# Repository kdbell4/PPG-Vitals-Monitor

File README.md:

# PPG Vitals Monitor

A finger-clip vitals monitor built from scratch. Monitors standard vitals (heart rate, blood oxygen).

- Created with kicad schematic, which prototyped on a breadboard
  
  - PCB design is on the roadmap

- Firmware samples the output of the sensor, and a live plot tool reads those serial samples and generates a graph to analyze the waveform

- Finger Jig, a CAD model for holding the LED and photodiode in alignment across a finger

## Repo layout

| Path              | Contents                                                   |
| ----------------- | ---------------------------------------------------------- |
| `ppg_platformio/` | Teensy 4.0 firmware (PlatformIO + Arduino framework)       |
| `ppg_circuit/`    | KiCad project — schematic and PCB for the analog front end |
| `CAD/`            | FreeCAD parts                                              |

## Hardware Used

- **Photodiode**: BPW34
- **Op-amp**: MCP6002
- **MCU**: Teensy 4.0

## Signal Path for Sensor

```
Red + IR LEDs (660nm / 940nm)
        |
        v
   Finger (tissue) -- absorbs pulsing blood
        |
        v
Photodiode + TIA -- converts light to voltage
        |
        v
Passive filter + gain -- isolates the pulse signal
        |
        v
MCU: ADC + firmware -- heart rate, SpO2, bio-ID match
        |
        v
     Display -- vitals + identity
```

## CAD

3D-printed parts (`CAD/`) hold the LED and photodiode in stable optical
alignment across the fingertip. Built in FreeCAD; STLs are exported for slicing and
printing.

# Credits

- [XenGi](https://github.com/XenGi) for the Teensy symbol and footprint libraries for kicad
  
  - https://github.com/XenGi/teensy_library

- https://github.com/XenGi/teensy.pretty

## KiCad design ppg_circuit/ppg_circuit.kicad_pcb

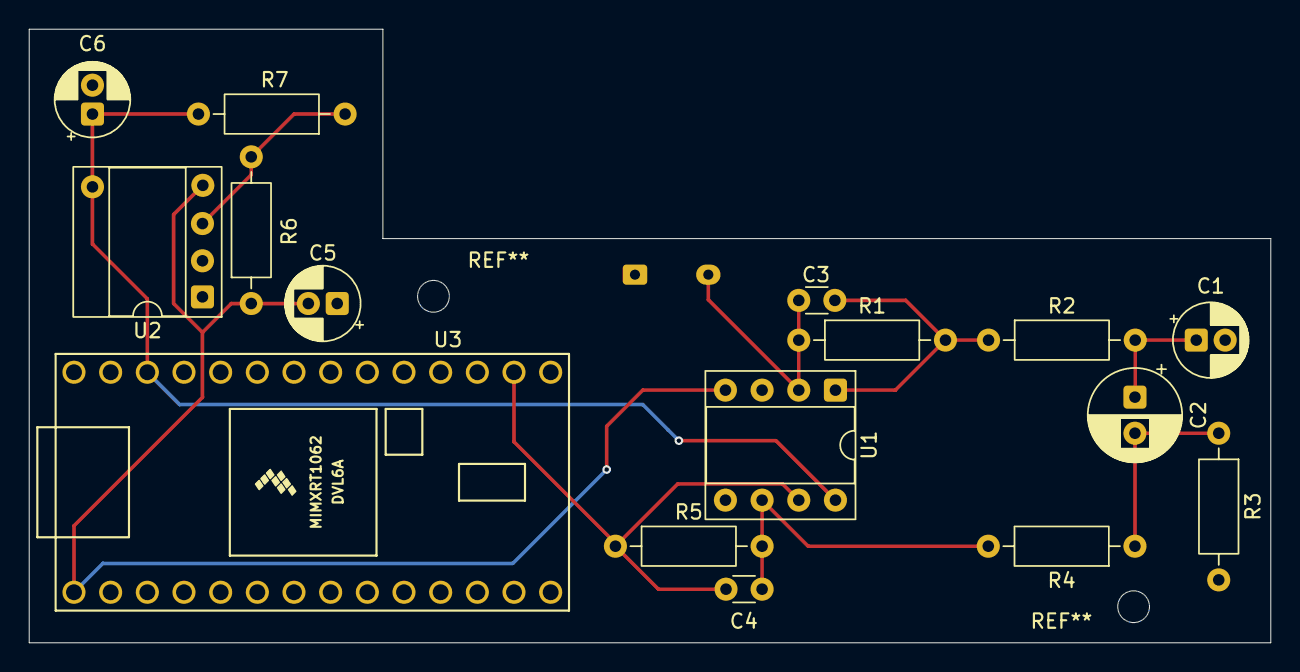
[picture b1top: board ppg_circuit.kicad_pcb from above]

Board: 2 copper layers, 86.0 x 42.5 mm, 17 parts (1 on the bottom side), 10 nets.

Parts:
C1, C5, C6: 10u; CP_Radial_D5.0mm_P2.00mm
C2: 100u; CP_Radial_D6.3mm_P2.50mm
C3, C4: 22p; C_Disc_D3.0mm_W1.6mm_P2.50mm
D1: BPW34; Osram_DIL2_4.3x4.65mm_P5.08mm
R1, R6, R7: 10k; R_Axial_DIN0207_L6.3mm_D2.5mm_P10.16mm_Horizontal
R2: 330; R_Axial_DIN0207_L6.3mm_D2.5mm_P10.16mm_Horizontal
R3: 5k; R_Axial_DIN0207_L6.3mm_D2.5mm_P10.16mm_Horizontal
R4: 2k; R_Axial_DIN0207_L6.3mm_D2.5mm_P10.16mm_Horizontal
R5: 100k; R_Axial_DIN0207_L6.3mm_D2.5mm_P10.16mm_Horizontal
U1: Opamp_Dual; DIP-8_W7.62mm_Socket
U2: MCP6001x-LT; DIP-8_W7.62mm_Socket
U3: Teensy4.0; Teensy40

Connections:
/high: C6.1, R7.2, U1.8 (V+), U2.5 (V+), U3.31 (3V3)
/in: C3.2, D1.2 (A), R1.1, U1.2 (-)
/low: C5.2, R6.1, U1.4 (V-), U2.2 (V-), U3.1 (GND)
/out1: C3.1, R1.2, R2.1, U1.1
/out2: C1.1, C2.1, R2.2
/out3: C2.2, R3.1, R4.1
/outf: C4.1, R5.1, U1.7, U3.21 (14_A0_TX3_SPDIF_OUT)
GND: C1.2, C5.1, C6.2, D1.1 (K), R3.2, U1.3 (+), U1.5 (+), U2.1, U2.4 (-)
unnamed: C4.2, R4.2, R5.2, U1.6 (-)
unnamed: R6.2, R7.1, U2.3 (+)
